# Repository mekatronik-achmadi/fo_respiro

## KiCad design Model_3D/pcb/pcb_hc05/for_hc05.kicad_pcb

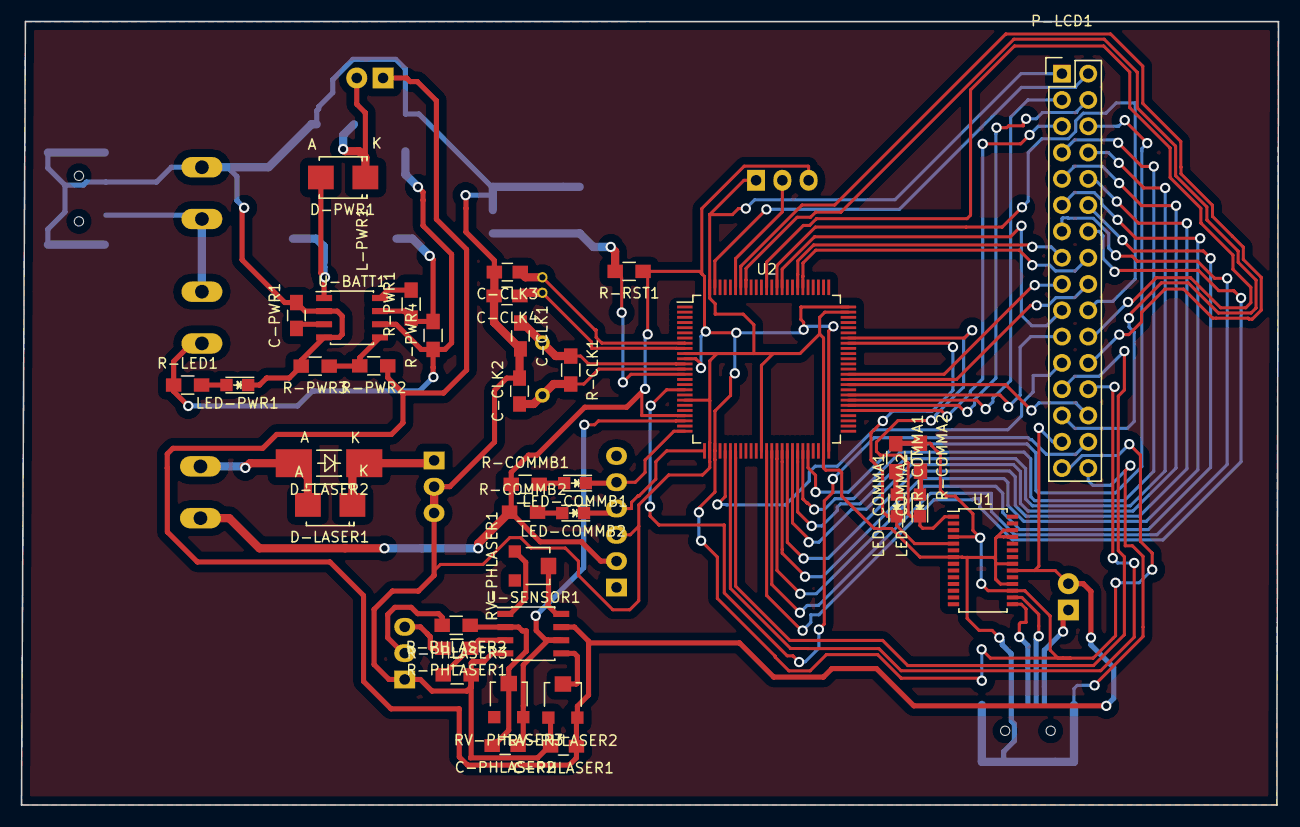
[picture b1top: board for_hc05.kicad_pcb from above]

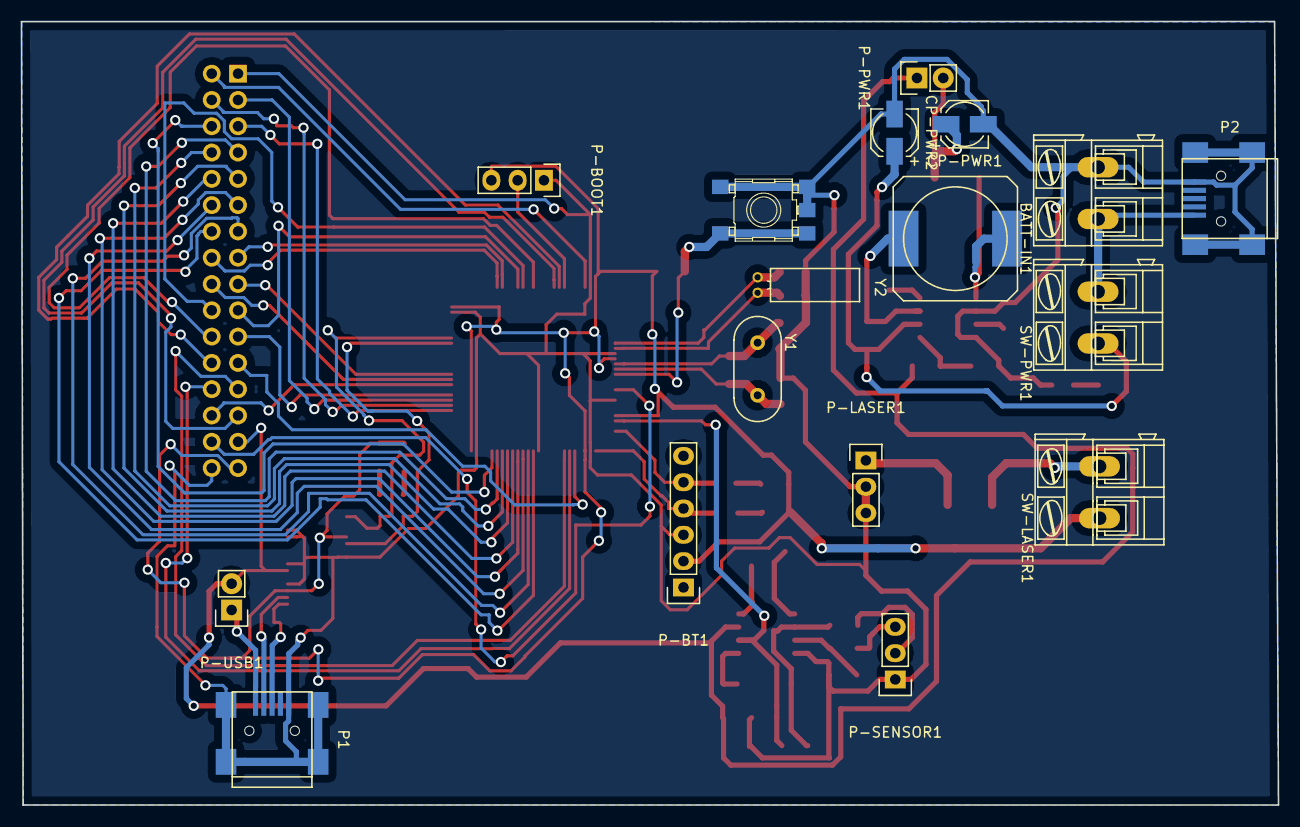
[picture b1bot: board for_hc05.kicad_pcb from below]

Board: 2 copper layers, 121.4 x 75.7 mm, 54 parts (17 on the bottom side), 67 nets.

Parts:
BATT-IN1: CONN_01X02; AK300-2
C-CLK1, C-CLK2, C-CLK3, C-CLK4: 22pF; C_0805_HandSoldering
C-PHLASER1, C-PHLASER2: 0.1uF; C_0805_HandSoldering
C-PWR1: 1nF; C_0805_HandSoldering
CP-PWR1: 100uF; c_elec_4x5.3
CP-PWR2: 10uF; c_elec_4x5.3
D-LASER1: D; SMB_Standard
D-LASER2: D; MELF_Handsoldering
D-PWR1: D_Schottky; SMB_Standard
L-PWR1: 100uH; SELF-WE-PD-XXL
LED-COMMA1, LED-COMMA2: LED; LED_0805
LED-COMMB1, LED-COMMB2: LED; LED_0805
LED-PWR1: LED; LED_0805
P1, P2: USB_OTG; USB_Mini-B
P-BOOT1: CONN_01X03; Pin_Header_Straight_1x03
P-BT1: CONN_01X06; Pin_Header_Straight_1x06
P-LASER1: CONN_01X03; Pin_Header_Straight_1x03
P-LCD1: CONN_02X16; Pin_Header_Straight_2x16
P-PWR1: CONN_01X02; Pin_Header_Straight_1x02
P-SENSOR1: CONN_01X03; Pin_Header_Straight_1x03
P-USB1: CONN_01X02; Pin_Header_Straight_1x02
R-CLK1: 1K; R_0805_HandSoldering
R-COMMA1, R-COMMA2: 330; R_0805_HandSoldering
R-COMMB1, R-COMMB2: 330; R_0805_HandSoldering
R-LED1: 330; R_0805_HandSoldering
R-PHLASER1, R-PHLASER2, R-PHLASER3: 100K; R_0805_HandSoldering
R-PWR1, R-PWR4: 180; R_0805_HandSoldering
R-PWR2: 12K; R_0805_HandSoldering
R-PWR3: 3K9; R_0805_HandSoldering
R-RST1: 4k7; R_0805_HandSoldering
RV-PHLASER1, RV-PHLASER2, RV-PHLASER3: 100K; Potentiometer_Trimmer-EVM3E
SW-LASER1: SW_Push; AK300-2
SW-PWR1: SW_Push; AK300-2
U1: FT232RL; TSSOP-28_4.4x9.7mm_Pitch0.65mm
U2: STM32F103VETx; LQFP-100_14x14mm_Pitch0.5mm
U5: SKHMP*E010_SKHMPXE010; SKHMPXE010
U-BATT1: MC33063/MC34063D_SO08; SOIC-8_3.9x4.9mm_Pitch1.27mm
U-SENSOR1: AD620; SOIC-8_3.9x4.9mm_Pitch1.27mm
Y1: 8MHz; HC-49V
Y2: 32.768kHz; Crystal_Round_Horizontal_3mm

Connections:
/ADC_SENSOR: C-PHLASER2.1, RV-PHLASER3.3, U2.23, U-SENSOR1.6
/BT_RX: LED-COMMB1.1, P-BT1.5, U2.25
/BT_TX: LED-COMMB2.1, P-BT1.4, U2.26
/LCD_BL: P-LCD1.28, U2.60
/LCD_CS: P-LCD1.22, U2.88
/LCD_D0: P-LCD1.18, U2.61
/LCD_D1: P-LCD1.17, U2.62
/LCD_D2: P-LCD1.16, U2.81
/LCD_D3: P-LCD1.15, U2.82
/LCD_D4: P-LCD1.14, U2.38
/LCD_D5: P-LCD1.13, U2.39
/LCD_D6: P-LCD1.12, U2.40
/LCD_D7: P-LCD1.11, U2.41
/LCD_D8: P-LCD1.10, U2.42
/LCD_D9: P-LCD1.9, U2.43
/LCD_D10: P-LCD1.8, U2.44
/LCD_D11: P-LCD1.7, U2.45
/LCD_D12: P-LCD1.6, U2.46
/LCD_D13: P-LCD1.5, U2.55
/LCD_D14: P-LCD1.4, U2.56
/LCD_D15: P-LCD1.3, U2.57
/LCD_RD: P-LCD1.19, U2.85
/LCD_RS: P-LCD1.21, U2.58
/LCD_RST: P-LCD1.2, U2.98
/LCD_WR: P-LCD1.20, U2.86
/PC2: P-LCD1.30, U2.17
/RX: LED-COMMA1.1, U1.5, U2.68
/TIN_CS: P-LCD1.24, U2.93
/TIN_INT: P-LCD1.27, U2.92
/TIN_MISO: P-LCD1.26, U2.31
/TIN_MOSI: P-LCD1.25, U2.32
/TIN_TCK: P-LCD1.23, U2.30
/TX: LED-COMMA2.1, U1.1, U2.69
GND: BATT-IN1.2, C-CLK1.2, C-CLK2.2, C-CLK3.2, C-CLK4.2, C-PHLASER1.2, C-PWR1.2, CP-PWR1.2, CP-PWR2.2, LED-PWR1.1, P1.5, P1.6, P2.5, P2.6, P-BOOT1.1, P-BT1.3, P-LASER1.2, P-LASER1.3, P-LCD1.1, P-LCD1.32, P-SENSOR1.1, R-PHLASER3.2, R-PWR3.2, RV-PHLASER2.1, U1.7, U1.18, U1.21, U1.25, U1.26, U2.10, U2.19, U2.27, U2.37, U2.49, U2.74, U2.99, U5.1, U5.2, U5.5, U-BATT1.2, U-BATT1.4, U-SENSOR1.4
unnamed: BATT-IN1.1, P2.1, SW-PWR1.2
unnamed: C-CLK1.1, R-CLK1.1, U2.12, Y1.1
unnamed: C-CLK2.1, R-CLK1.2, U2.13, Y1.2
unnamed: C-CLK3.1, U2.8, Y2.1
unnamed: C-CLK4.1, U2.9, Y2.2
unnamed: C-PHLASER2.2, R-PHLASER2.1, RV-PHLASER3.2, U-SENSOR1.2
unnamed: C-PWR1.1, U-BATT1.3
unnamed: CP-PWR1.1, D-PWR1.1, P-PWR1.2
unnamed: CP-PWR2.1, R-LED1.1, R-PWR4.1, SW-PWR1.1, U-BATT1.6
unnamed: D-LASER1.1, D-LASER2.1, P-LASER1.1
unnamed: D-LASER1.2, D-LASER2.2, SW-LASER1.2
unnamed: D-PWR1.2, L-PWR1.2, U-BATT1.1
unnamed: L-PWR1.1, R-PWR1.1, R-PWR4.2, U-BATT1.7
unnamed: LED-COMMA1.2, R-COMMA1.2
unnamed: LED-COMMA2.2, R-COMMA2.2
unnamed: LED-COMMB1.2, R-COMMB1.2
unnamed: LED-COMMB2.2, R-COMMB2.2
unnamed: LED-PWR1.2, R-LED1.2
unnamed: P1.2, U1.16
unnamed: P1.3, U1.15
unnamed: P-BOOT1.2, U2.94
unnamed: P-SENSOR1.2, R-PHLASER2.2
unnamed: P-SENSOR1.3, R-PHLASER1.2
unnamed: P1.1, P-USB1.1
unnamed: R-PHLASER1.1, R-PHLASER3.1, U-SENSOR1.3
unnamed: R-PWR1.2, U-BATT1.8
unnamed: R-PWR2.2, R-PWR3.1, U-BATT1.5
unnamed: R-RST1.2, U2.14, U5.3, U5.4
unnamed: RV-PHLASER1.1, U-SENSOR1.1
unnamed: RV-PHLASER1.2, U-SENSOR1.8
unnamed: RV-PHLASER2.2, U-SENSOR1.5
VCC: C-PHLASER1.1, P-LCD1.29, P-PWR1.1, P-USB1.2, R-PWR2.1, RV-PHLASER2.3, U1.20, U-SENSOR1.7
VDD: P-BOOT1.3, P-BT1.2, P-LCD1.31, R-COMMA1.1, R-COMMA2.1, R-COMMB1.1, R-COMMB2.1, R-RST1.1, SW-LASER1.1, U1.4, U1.17, U2.11, U2.22, U2.28, U2.50, U2.75, U2.100
